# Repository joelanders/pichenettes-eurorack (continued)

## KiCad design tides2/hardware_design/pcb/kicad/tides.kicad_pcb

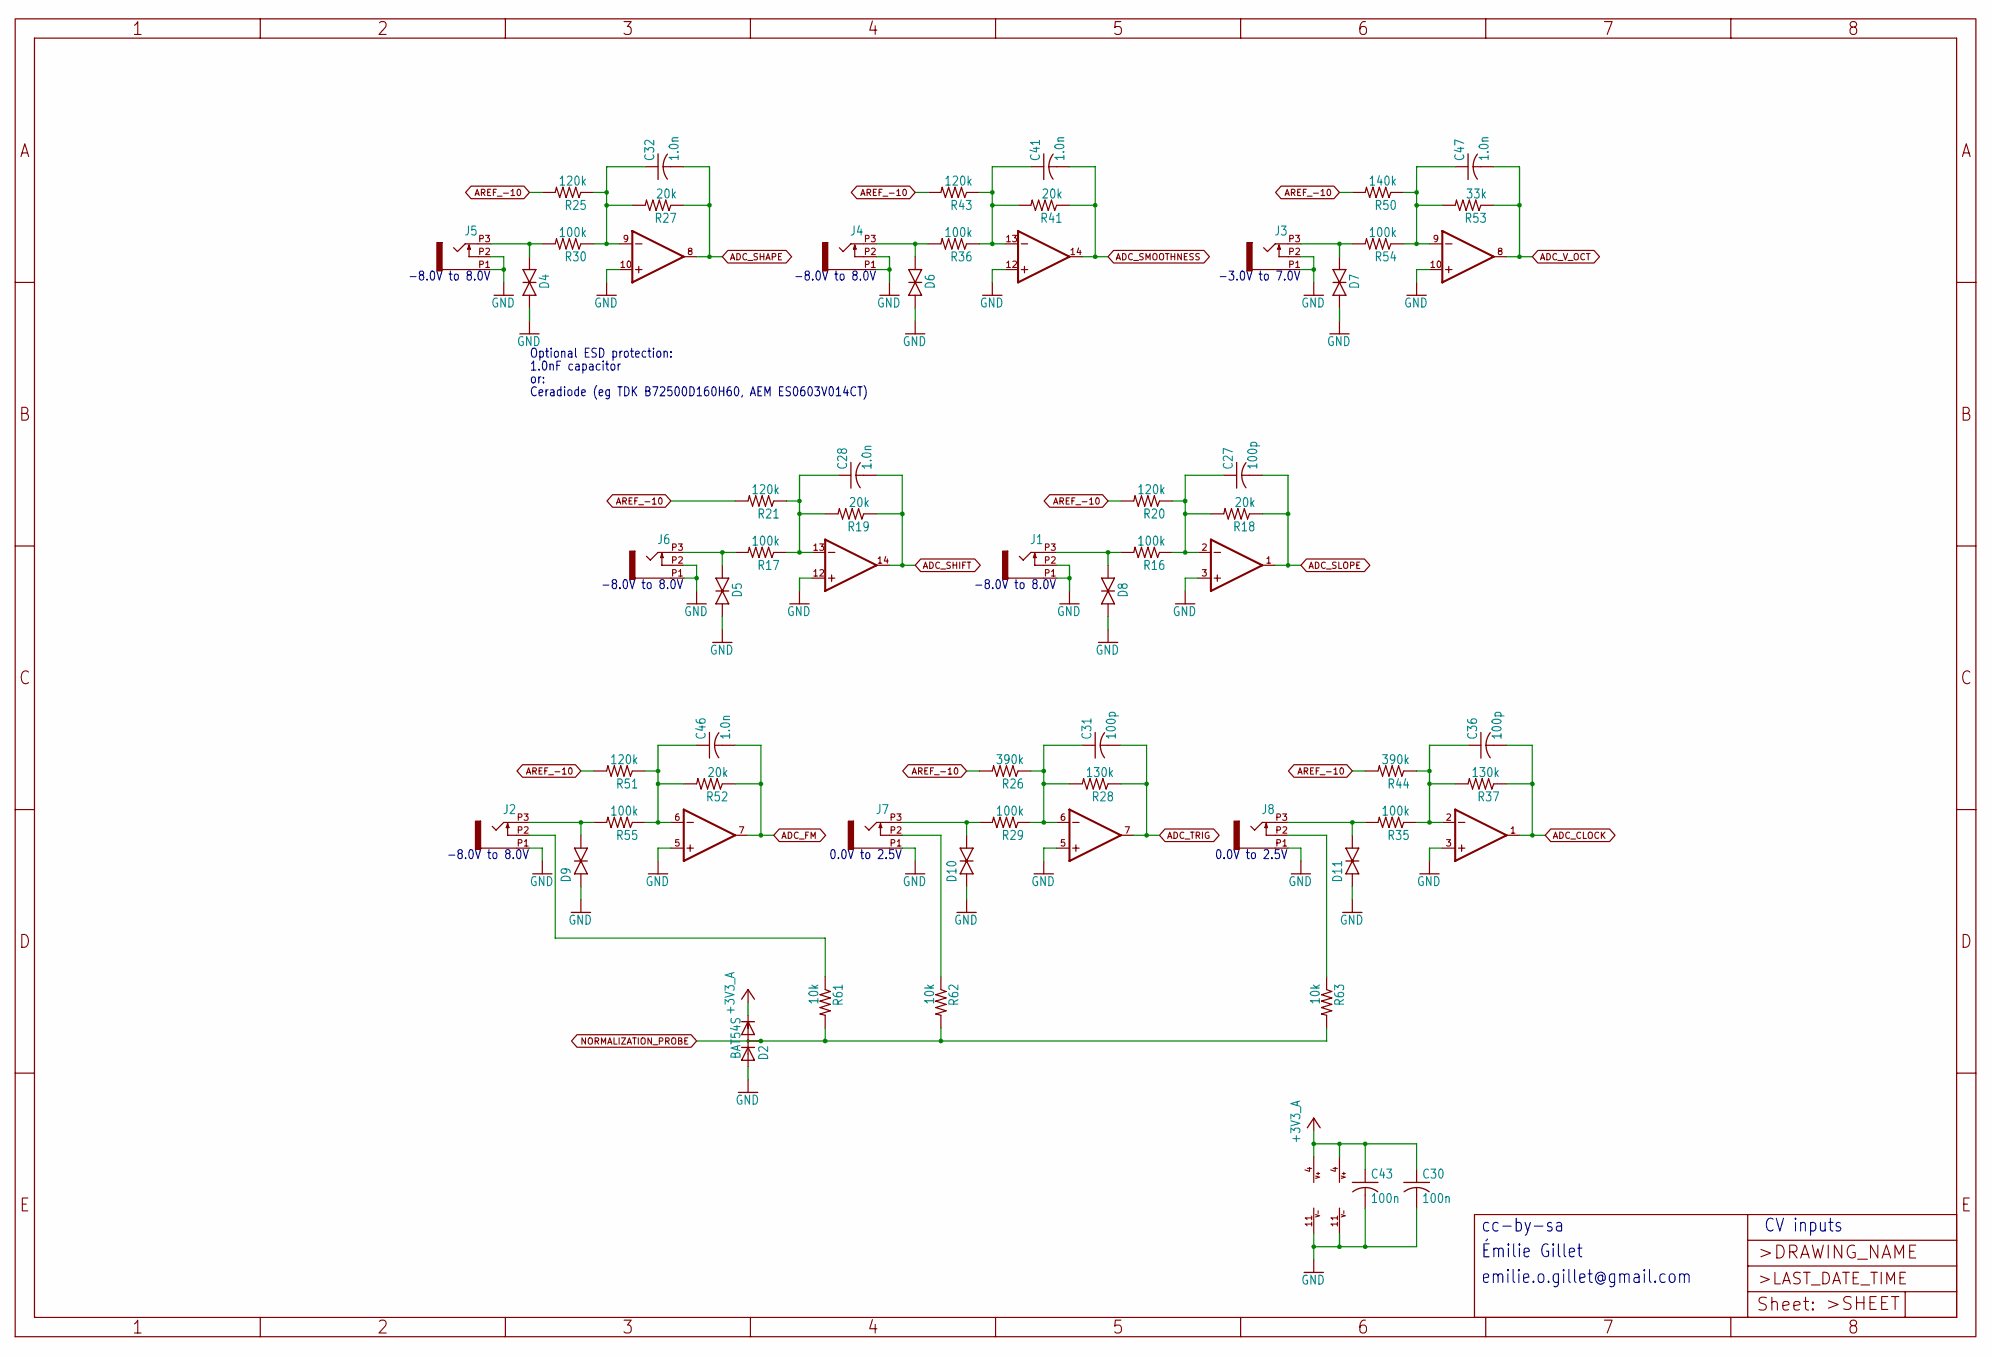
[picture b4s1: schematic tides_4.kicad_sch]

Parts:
C27, C31, C36: 100p; C0402
C28, C32, C41, C46, C47: 1.0n; C0402
C30, C43: 100n; C0402
D2: BAT54S; SOT23
D4, D5, D6, D7, D8, D9, D10, D11: TVS; 0603
IC6, IC7: MCP6004; TSSOP14_065
J1, J2, J3, J4, J5, J6, J7, J8: PJ301_THONKICONN6; WQP_PJ_301M6
R16, R17, R29, R30, R35, R36, R54, R55: 100k; R0402
R18, R19, R27, R41, R52: 20k; R0402
R20, R21, R25, R43, R51: 120k; R0402
R26, R44: 390k; R0402
R28, R37: 130k; R0402
R50: 140k; R0402
R53: 33k; R0402
R61, R62, R63: 10k; R0402

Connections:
+3V3_A: C30.1, C43.1, D2.2 (C), IC6.4 (V+), IC7.4 (V+); also elsewhere on the board
ADC_CLOCK: C36.2, IC7.1 (OUT), R37.1; also elsewhere on the board
ADC_FM: C46.2, IC7.7 (OUT), R52.1; also elsewhere on the board
ADC_SHAPE: C32.2, IC6.8 (OUT), R27.1; also elsewhere on the board
ADC_SHIFT: C28.2, IC6.14 (OUT), R19.1; also elsewhere on the board
ADC_SLOPE: C27.2, IC6.1 (OUT), R18.1; also elsewhere on the board
ADC_SMOOTHNESS: C41.2, IC7.14 (OUT), R41.1; also elsewhere on the board
ADC_TRIG: C31.2, IC6.7 (OUT), R28.1; also elsewhere on the board
ADC_V_OCT: C47.2, IC7.8 (OUT), R53.1; also elsewhere on the board
AREF_-10: R20.2, R21.2, R25.2, R26.2, R43.2, R44.2, R50.2, R51.2; also elsewhere on the board
GND: C30.2, C43.2, D2.1 (A), D4.1 (A), D5.1 (A), D6.1 (A), D7.1 (A), D8.1 (A), D9.1 (A), D10.1 (A), D11.1 (A), IC6.3 (+IN), IC6.5 (+IN), IC6.10 (+IN), IC6.11 (V-), IC6.12 (+IN), IC7.3 (+IN), IC7.5 (+IN), IC7.10 (+IN), IC7.11 (V-), IC7.12 (+IN), J1.P1 (1), J1.P2 (2), J2.P1 (1), J3.P1 (1), J3.P2 (2), J4.P1 (1), J4.P2 (2), J5.P1 (1), J5.P2 (2), J6.P1 (1), J6.P2 (2), J7.P1 (1), J8.P1 (1); also elsewhere on the board
NORMALIZATION_PROBE: D2.3 (AC), R61.2, R62.2, R63.2; also elsewhere on the board
unnamed: C27.1, IC6.2 (-IN), R16.1, R18.2, R20.1
unnamed: C28.1, IC6.13 (-IN), R17.1, R19.2, R21.1
unnamed: C31.1, IC6.6 (-IN), R26.1, R28.2, R29.1
unnamed: C32.1, IC6.9 (-IN), R25.1, R27.2, R30.1
unnamed: C36.1, IC7.2 (-IN), R35.1, R37.2, R44.1
unnamed: C41.1, IC7.13 (-IN), R36.1, R41.2, R43.1
unnamed: C46.1, IC7.6 (-IN), R51.1, R52.2, R55.1
unnamed: C47.1, IC7.9 (-IN), R50.1, R53.2, R54.1
unnamed: D4.2 (C), J5.P3 (3), R30.2
unnamed: D5.2 (C), J6.P3 (3), R17.2
unnamed: D6.2 (C), J4.P3 (3), R36.2
unnamed: D7.2 (C), J3.P3 (3), R54.2
unnamed: D8.2 (C), J1.P3 (3), R16.2
unnamed: D9.2 (C), J2.P3 (3), R55.2
unnamed: D10.2 (C), J7.P3 (3), R29.2
unnamed: D11.2 (C), J8.P3 (3), R35.2
unnamed: J2.P2 (2), R61.1
unnamed: J7.P2 (2), R62.1
unnamed: J8.P2 (2), R63.1

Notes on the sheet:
-8.0V to 8.0V
or:
1.0nF capacitor
-3.0V to 7.0V
0.0V to 2.5V
Optional ESD protection:
emilie.o.gillet@gmail.com
Ceradiode (eg TDK B72500D160H60, AEM ES0603V014CT)
Émilie Gillet
CV inputs
cc-by-sa

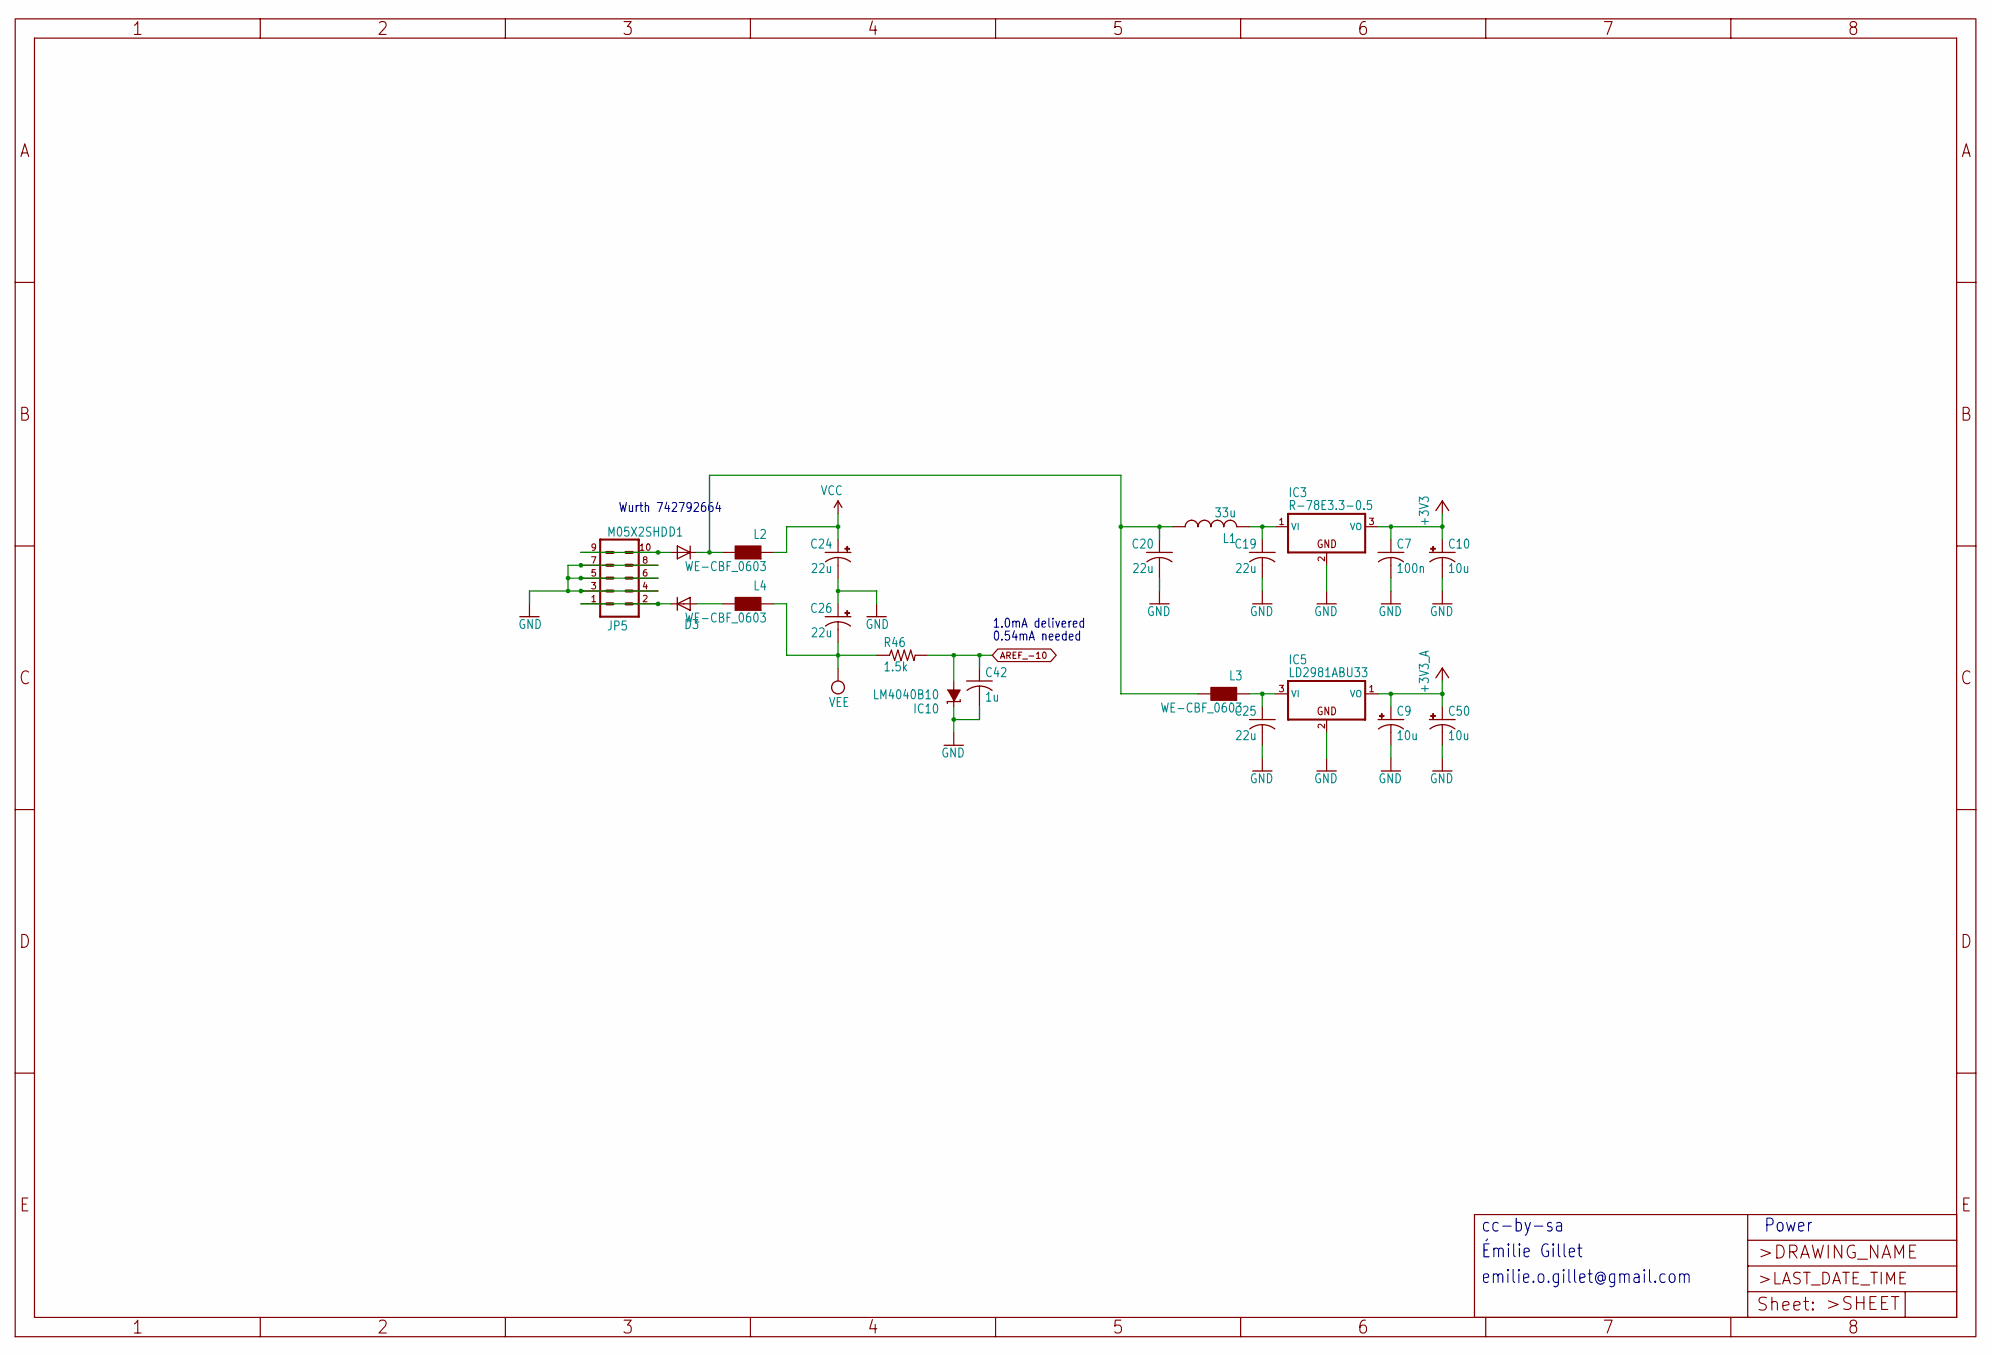
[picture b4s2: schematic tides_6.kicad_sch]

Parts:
C7: 100n; C0402
C9, C10, C50: 10u; PANASONIC_B
C19, C20, C25: 22u; C1206
C24, C26: 22u; PANASONIC_B
C42: 1u; C0402
D1, D3: 1N5819HW; SOD123
IC3: R-78E3.3-0.5; WE78
IC5: LD2981ABU33; SOT89
IC10: LM4040B10; DBZ_R-PDSO-G3
JP5: M05X2SHD; 2X5-SHROUDED
L1: 33u; L2012C
L2, L3, L4: WE-CBF_0603; 0603
R46: 1.5k; R0402

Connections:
+3V3: C7.1, C10.+, IC3.3 (VO); also elsewhere on the board
+3V3_A: C9.+, C50.+, IC5.1 (VO); also elsewhere on the board
AREF_-10: C42.1, IC10.2 (A), R46.2; also elsewhere on the board
GND: C7.2, C9.-, C10.-, C19.2, C20.2, C24.-, C25.2, C26.+, C42.2, C50.-, IC3.2 (GND), IC5.2 (GND), IC10.1 (C), JP5.3, JP5.4, JP5.5, JP5.6, JP5.7, JP5.8; also elsewhere on the board
unnamed: C19.1, IC3.1 (VI), L1.2
unnamed: C20.1, D1.C, L1.1, L2.2, L3.2
unnamed: C25.1, IC5.3 (VI), L3.1
unnamed: D1.A, JP5.9, JP5.10
unnamed: D3.A, L4.2
unnamed: D3.C, JP5.1, JP5.2
VCC: C24.+, L2.1; also elsewhere on the board
VEE: C26.-, L4.1, R46.1; also elsewhere on the board

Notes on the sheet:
emilie.o.gillet@gmail.com
Émilie Gillet
Wurth 742792664
0.54mA needed
cc-by-sa
Power
1.0mA delivered

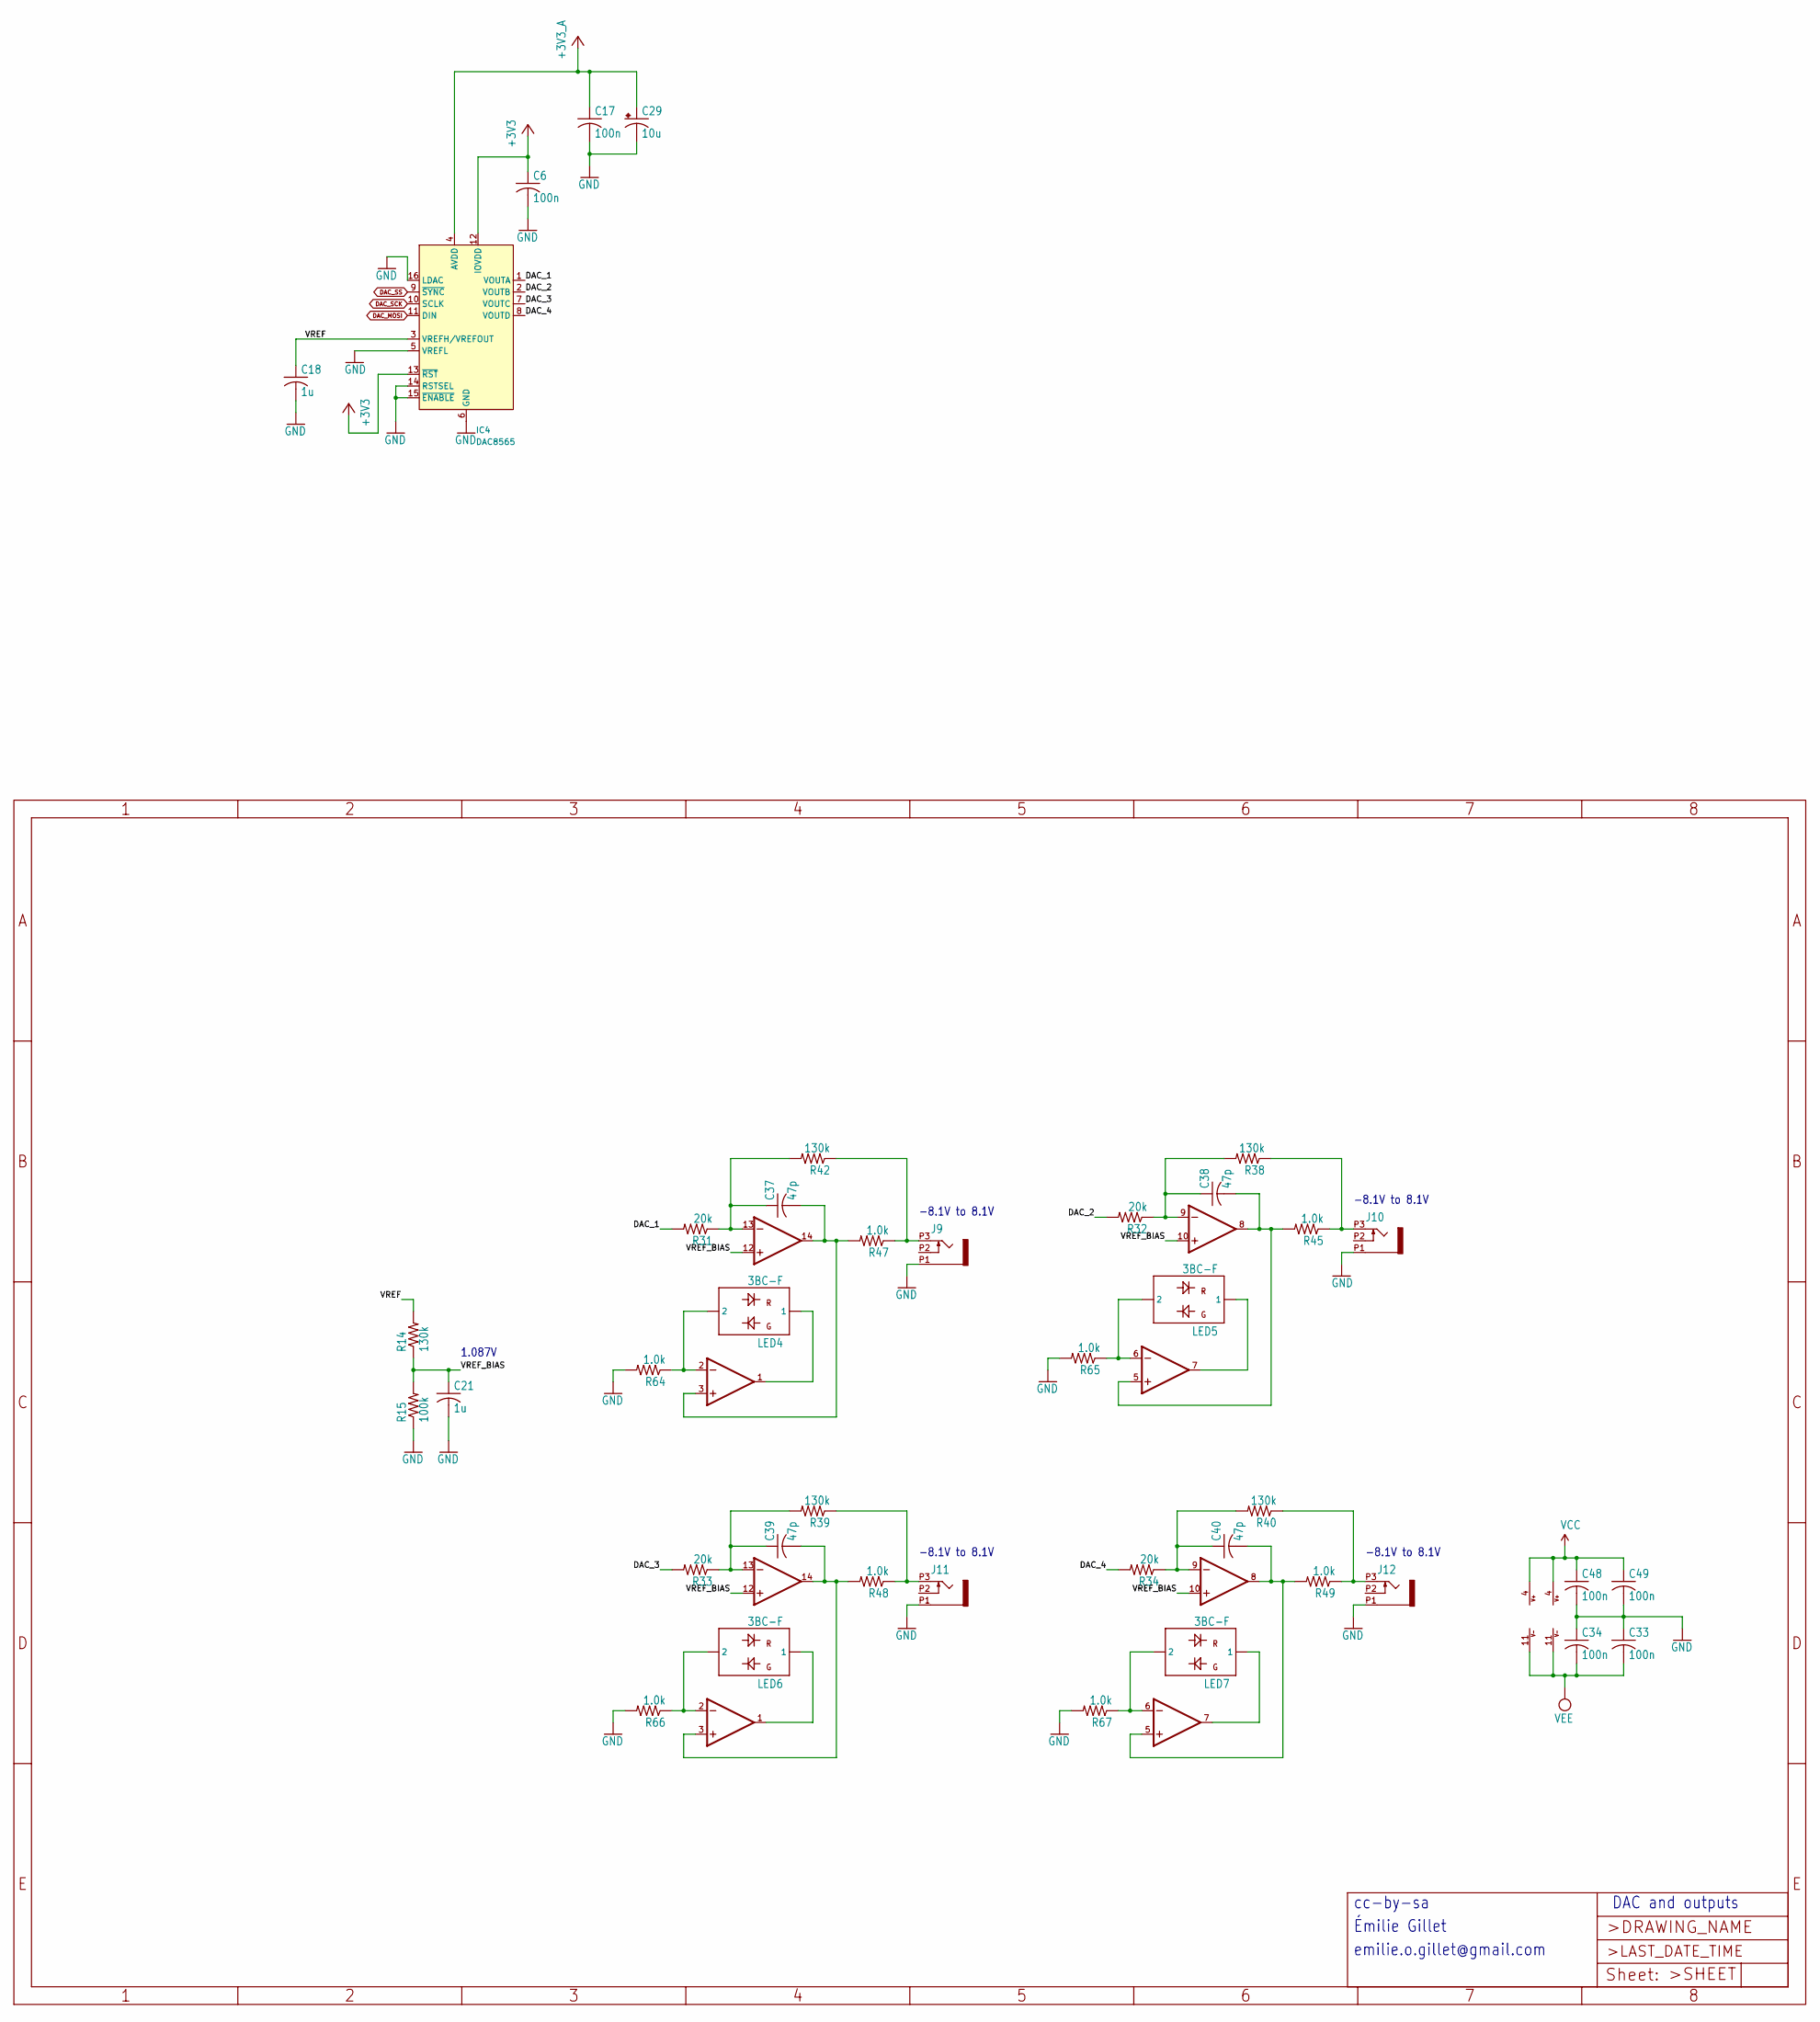
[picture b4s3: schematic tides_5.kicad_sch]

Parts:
C6, C17, C33, C34, C48, C49: 100n; C0402
C18, C21: 1u; C0402
C29: 10u; PANASONIC_B
C37, C38, C39, C40: 47p; C0402
IC4: DAC8565; TSSOP-16_4.4x5mm_P0.65mm
IC8, IC9: TLV4172; SOIC-14_3.9x8.7mm_P1.27mm
J9, J10, J11, J12: PJ301_THONKICONN6; WQP_PJ_301M6
LED4, LED5, LED6, LED7: 3BC-F; LED3MM
R14, R38, R39, R40, R42: 130k; R0402
R15: 100k; R0402
R31, R32, R33, R34: 20k; R0402
R45, R47, R48, R49: 1.0k; R0603
R64, R65, R66, R67: 1.0k; R0402

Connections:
+3V3: C6.1, IC4.12 (IOVDD), IC4.13 (~RST); also elsewhere on the board
+3V3_A: C17.1, C29.+, IC4.4 (AVDD); also elsewhere on the board
/tides_5/DAC_1: IC4.1 (VOUTA), R31.2
/tides_5/DAC_2: IC4.2 (VOUTB), R32.2
/tides_5/DAC_3: IC4.7 (VOUTC), R33.2
/tides_5/DAC_4: IC4.8 (VOUTD), R34.2
/tides_5/VREF: C18.1, IC4.3 (VREFH/VREFOUT), R14.2
/tides_5/VREF_BIAS: C21.1, IC8.10 (+IN), IC8.12 (+IN), IC9.10 (+IN), IC9.12 (+IN), R14.1, R15.2
DAC_MOSI: IC4.11 (DIN); also elsewhere on the board
DAC_SCK: IC4.10 (SCLK); also elsewhere on the board
DAC_SS: IC4.9 (~SYNC); also elsewhere on the board
GND: C6.2, C17.2, C18.2, C21.2, C29.-, C33.1, C34.1, C48.2, C49.2, IC4.5 (VREFL), IC4.6 (GND), IC4.14 (RSTSEL), IC4.15 (~ENABLE), IC4.16 (LDAC), J9.P1 (1), J10.P1 (1), J11.P1 (1), J12.P1 (1), R15.1, R64.2, R65.2, R66.2, R67.2; also elsewhere on the board
unnamed: C37.1, IC9.13 (-IN), R31.1, R42.2
unnamed: C37.2, IC9.3 (+IN), IC9.14 (OUT), R47.2
unnamed: C38.1, IC9.9 (-IN), R32.1, R38.2
unnamed: C38.2, IC9.5 (+IN), IC9.8 (OUT), R45.2
unnamed: C39.1, IC8.13 (-IN), R33.1, R39.2
unnamed: C39.2, IC8.3 (+IN), IC8.14 (OUT), R48.2
unnamed: C40.1, IC8.9 (-IN), R34.1, R40.2
unnamed: C40.2, IC8.5 (+IN), IC8.8 (OUT), R49.2
unnamed: IC8.1 (OUT), LED6.1
unnamed: IC8.2 (-IN), LED6.2, R66.1
unnamed: IC8.6 (-IN), LED7.2, R67.1
unnamed: IC8.7 (OUT), LED7.1
unnamed: IC9.1 (OUT), LED4.1
unnamed: IC9.2 (-IN), LED4.2, R64.1
unnamed: IC9.6 (-IN), LED5.2, R65.1
unnamed: IC9.7 (OUT), LED5.1
unnamed: J9.P3 (3), R42.1, R47.1
unnamed: J10.P3 (3), R38.1, R45.1
unnamed: J11.P3 (3), R39.1, R48.1
unnamed: J12.P3 (3), R40.1, R49.1
VCC: C48.1, C49.1, IC8.4 (V+), IC9.4 (V+); also elsewhere on the board
VEE: C33.2, C34.2, IC8.11 (V-), IC9.11 (V-); also elsewhere on the board

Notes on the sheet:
-8.1V to 8.1V
emilie.o.gillet@gmail.com
cc-by-sa
DAC and outputs
1.087V
Émilie Gillet

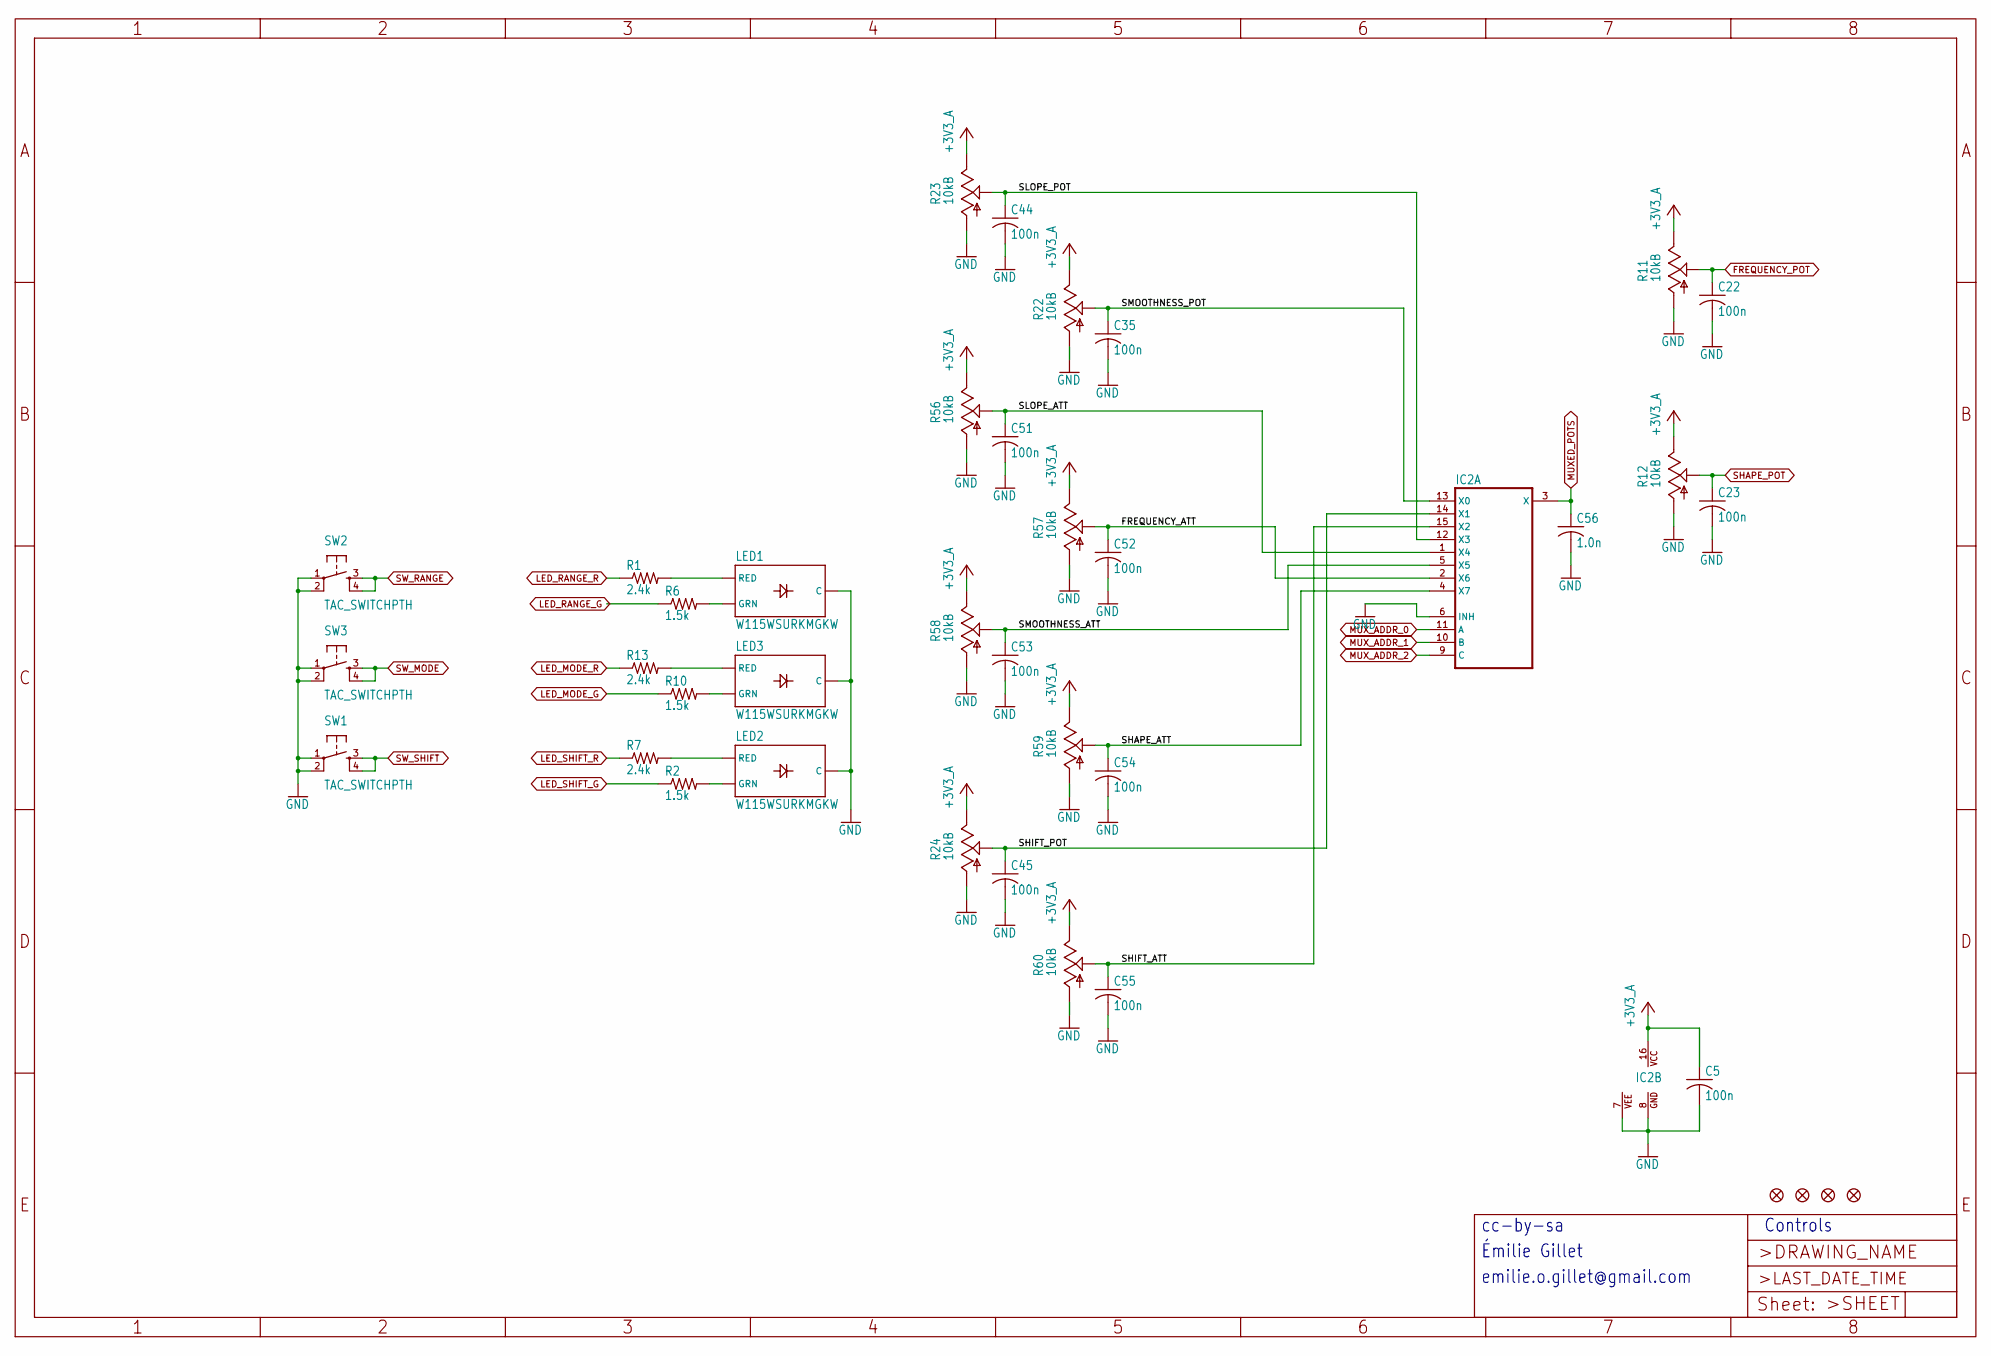
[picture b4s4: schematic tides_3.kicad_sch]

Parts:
C5, C22, C23, C35, C44, C45, C51, C52, C53, C54, C55: 100n; C0402
C56: 1.0n; C0402
IC2: 4051PW; TSSOP16_065
JP1, JP2, JP3, JP4: FIDUCIAL1X2; FIDUCIAL-1X2
LED1, LED2, LED3: W115WSURKMGKW; LED-BICOLOR-THROUGHHOLE-2.54
R1, R7, R13: 2.4k; R0402
R2, R6, R10: 1.5k; R0402
R11, R12, R22, R23, R24: 10kB; ALPS_POT_VERTICAL_PS
R56, R57, R58, R59, R60: 10kB; ALPS_POT_VERTICAL
SW1, SW2, SW3: TAC_SWITCHPTH; TACTILE-PTH

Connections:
+3V3_A: C5.1, IC2.16 (VCC), R11.P$1 (E), R12.P$1 (E), R22.P$1 (E), R23.P$1 (E), R24.P$1 (E), R56.P$1 (E), R57.P$1 (E), R58.P$1 (E), R59.P$1 (E), R60.P$1 (E); also elsewhere on the board
/tides_3/FREQUENCY_ATT: C52.1, IC2.2 (X6), R57.P$2 (S)
/tides_3/SHAPE_ATT: C54.1, IC2.4 (X7), R59.P$2 (S)
/tides_3/SHIFT_ATT: C55.1, IC2.15 (X2), R60.P$2 (S)
/tides_3/SHIFT_POT: C45.1, IC2.14 (X1), R24.P$2 (S)
/tides_3/SLOPE_ATT: C51.1, IC2.1 (X4), R56.P$2 (S)
/tides_3/SLOPE_POT: C44.1, IC2.12 (X3), R23.P$2 (S)
/tides_3/SMOOTHNESS_ATT: C53.1, IC2.5 (X5), R58.P$2 (S)
/tides_3/SMOOTHNESS_POT: C35.1, IC2.13 (X0), R22.P$2 (S)
FREQUENCY_POT: C22.1, R11.P$2 (S); also elsewhere on the board
GND: C5.2, C22.2, C23.2, C35.2, C44.2, C45.2, C51.2, C52.2, C53.2, C54.2, C55.2, C56.2, IC2.6 (INH), IC2.7 (VEE), IC2.8 (GND), LED1.2 (C), LED2.2 (C), LED3.2 (C), R11.P$3 (A), R12.P$3 (A), R22.P$3 (A), R23.P$3 (A), R24.P$3 (A), R56.P$3 (A), R57.P$3 (A), R58.P$3 (A), R59.P$3 (A), R60.P$3 (A), SW1.1, SW1.2, SW2.1, SW2.2, SW3.1, SW3.2; also elsewhere on the board
LED_MODE_G: R10.1; also elsewhere on the board
LED_MODE_R: R13.1; also elsewhere on the board
LED_RANGE_G: R6.1; also elsewhere on the board
LED_RANGE_R: R1.1; also elsewhere on the board
LED_SHIFT_G: R2.1; also elsewhere on the board
LED_SHIFT_R: R7.1; also elsewhere on the board
MUXED_POTS: C56.1, IC2.3 (X); also elsewhere on the board
MUX_ADDR_0: IC2.11 (A); also elsewhere on the board
MUX_ADDR_1: IC2.10 (B); also elsewhere on the board
MUX_ADDR_2: IC2.9 (C); also elsewhere on the board
unnamed: LED1.1 (GRN), R6.2
unnamed: LED1.3 (RED), R1.2
unnamed: LED2.1 (GRN), R2.2
unnamed: LED2.3 (RED), R7.2
unnamed: LED3.1 (GRN), R10.2
unnamed: LED3.3 (RED), R13.2
SHAPE_POT: C23.1, R12.P$2 (S); also elsewhere on the board
SW_MODE: SW3.3, SW3.4; also elsewhere on the board
SW_RANGE: SW2.3, SW2.4; also elsewhere on the board
SW_SHIFT: SW1.3, SW1.4; also elsewhere on the board

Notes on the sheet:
Émilie Gillet
emilie.o.gillet@gmail.com
cc-by-sa
Controls
